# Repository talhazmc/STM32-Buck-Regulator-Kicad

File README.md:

# STM32F4 Test Board with Buck Regulator

This repository contains my KiCad PCB design project for an STM32F4-based test and development board with an integrated buck regulator power section.

The board was designed as a compact embedded systems development platform that includes an STM32F4 microcontroller, programming/debugging interfaces, communication headers, status indicators, and onboard power regulation.

---

## Project Overview

The main purpose of this project was to design a custom STM32F4 test board using KiCad.

The board includes the essential hardware required for working with an STM32F4 microcontroller, such as power input, voltage regulation, SWD programming interface, UART and I2C headers, boot/run control, USB connection, and status LEDs.

This project combines embedded system PCB design and power supply design on a single board.

---

## 3D PCB View

The 3D view shows the physical placement of the STM32F4 microcontroller, SWD header, UART and I2C connectors, USB section, power input terminal, buck regulator components, status LEDs, and mounting holes.

---

## PCB Layout

The PCB layout was created in KiCad.

The STM32F4 microcontroller was placed near the center of the board. Communication and programming headers were positioned around the MCU for easier access. The power regulation section was placed on the right side of the board, close to the power input terminal.

---

## Main Features

- STM32F4 microcontroller-based custom test board
- Integrated buck regulator power section
- SWD programming/debugging connector
- UART communication header
- I2C communication header
- USB connection section
- BOOT and RUN control
- Status LED
- 3.3V power indicator LED
- External power input terminal
- Mounting holes for mechanical fixing

---

## Main Components

- STM32F4 microcontroller
- Buck regulator components
- Inductor
- Power input terminal block
- USB connector section
- SWD header
- UART header
- I2C header
- BOOT switch
- RUN switch
- Status LEDs
- Resistors and capacitors
- Mounting holes

---

## Working Principle

The board is designed around an STM32F4 microcontroller.

The external DC input is connected through the power terminal. The onboard buck regulator section converts the input voltage to the required lower voltage level for the system.

The SWD connector allows the STM32F4 microcontroller to be programmed and debugged. UART and I2C headers provide communication interfaces for external modules, sensors, or other embedded systems.

The BOOT and RUN controls are used during programming, reset, and startup operations. Status LEDs provide visual feedback about the board state and power status.

---

## PCB Design Notes

- The STM32F4 MCU was placed centrally for organized signal routing.
- SWD, UART, and I2C headers were placed near the board edges for easy access.
- The buck regulator section was separated from the microcontroller area.
- Wider traces were used in the power section.
- Mounting holes were added for mechanical stability.
- The board was checked using KiCad 3D Viewer.

---

## What I Learned

Through this project, I gained practical experience in:

- Designing STM32-based embedded system PCBs
- Using KiCad for schematic, PCB layout, and 3D visualization
- Integrating MCU, power, programming, and communication sections
- Designing a buck regulator power stage on the same PCB
- Routing microcontroller signals
- Planning PCB layout for debugging and testing
- Creating a more professional embedded development board structure

---

## Tools and Technologies

- KiCad
- STM32F4
- Buck regulator
- Embedded systems
- PCB design
- SWD programming
- UART communication
- I2C communication
- Power electronics

---

## Author

**Talha Üzümcü**  
Electrical and Electronics Engineer  
GitHub: [talhazmc](https://github.com/talhazmc)

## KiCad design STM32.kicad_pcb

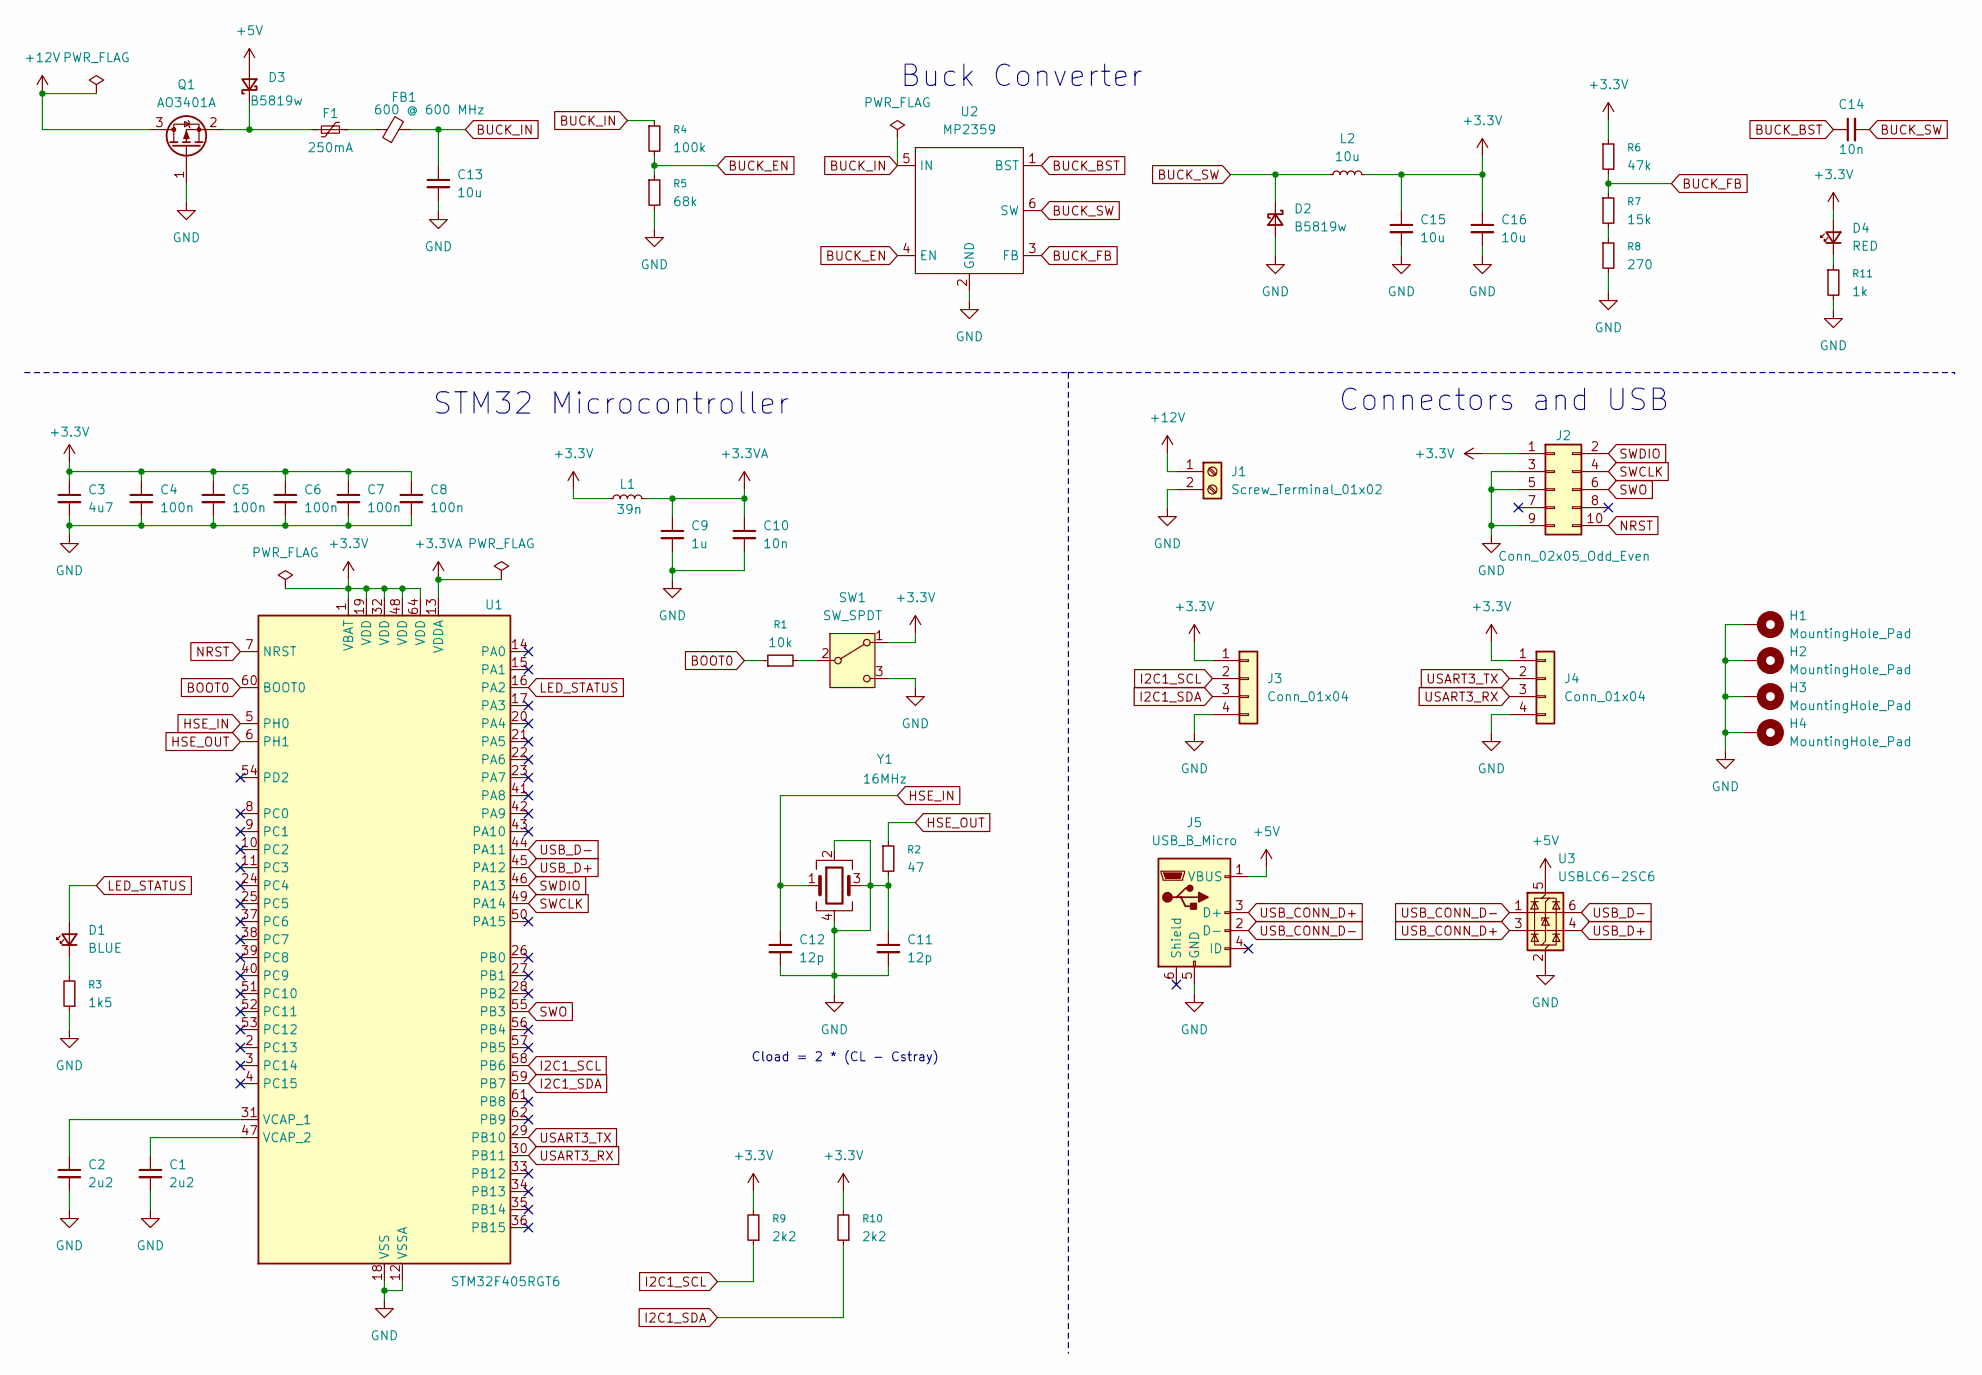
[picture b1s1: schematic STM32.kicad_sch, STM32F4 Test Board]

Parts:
C1, C2: 2u2; C_0603_1608Metric
C3: 4u7; C_0603_1608Metric
C4, C5, C6, C7, C8: 100n; C_0402_1005Metric
C9: 1u; C_0402_1005Metric
C10: 10n; C_0402_1005Metric
C11, C12: 12p; C_0402_1005Metric
C13, C15, C16: 10u; C_1206_3216Metric
C14: 10n; C_0603_1608Metric
D1: BLUE; LED_0603_1608Metric
D2, D3: B5819w; D_SOD-123
D4: RED; LED_0603_1608Metric
F1: 250mA; Fuse_1206_3216Metric
FB1: 600 @ 600 MHz; L_0805_2012Metric
H1, H2, H3, H4: MountingHole_Pad; MountingHole_4.3mm_M4_Pad_Via
J1: Screw_Terminal_01x02; TerminalBlock_Phoenix_PT-1,5-2-3.5-H_1x02_P3.50mm_Horizontal
J2: Conn_02x05_Odd_Even; PinHeader_2x05_P1.27mm_Vertical_SMD
J3, J4: Conn_01x04; Molex_PicoBlade_53048-0410_1x04_P1.25mm_Horizontal
J5: USB_B_Micro; USB_Micro-B_Molex-105017-0001
L1: 39n; L_0402_1005Metric
L2: 10u; L_Sunlord_MWSA0503S
Q1: AO3401A; SOT-23
R1: 10k; R_0402_1005Metric
R2: 47; R_0402_1005Metric
R3: 1k5; R_0603_1608Metric
R4: 100k; R_0603_1608Metric
R5: 68k; R_0603_1608Metric
R6: 47k; R_0603_1608Metric
R7: 15k; R_0603_1608Metric
R8: 270; R_0603_1608Metric
R9, R10: 2k2; R_0402_1005Metric
R11: 1k; R_0603_1608Metric
SW1: SW_SPDT; SW_SPDT_PCM12
U1: STM32F405RGT6; LQFP-64_10x10mm_P0.5mm
U2: MP2359; SOT-23-6
U3: USBLC6-2SC6; SOT-23-6
Y1: 16MHz; Crystal_SMD_3225-4Pin_3.2x2.5mm

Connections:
+3.3V: C3.1, C4.1, C5.1, C6.1, C7.1, C8.1, C15.1, C16.1, D4.2 (A), J2.1, J3.1, J4.1, L1.1, L2.2, R6.1, R9.2, R10.2, SW1.1 (A), U1.1 (VBAT), U1.19 (VDD), U1.32 (VDD), U1.48 (VDD), U1.64 (VDD)
+3.3VA: C9.1, C10.1, L1.2, U1.13 (VDDA)
+5V: D3.2 (A), J5.1 (VBUS), U3.5 (VBUS)
+12V: J1.1, Q1.3 (D)
BOOT0: R1.1, U1.60 (BOOT0)
BUCK_BST: C14.1, U2.1 (BST)
BUCK_EN: R4.2, R5.1, U2.4 (EN)
BUCK_FB: R6.2, R7.1, U2.3 (FB)
BUCK_IN: C13.1, FB1.2, R4.1, U2.5 (IN)
BUCK_SW: C14.2, D2.1 (K), L2.1, U2.6 (SW)
GND: C1.2, C2.2, C3.2, C4.2, C5.2, C6.2, C7.2, C8.2, C9.2, C10.2, C11.1, C11.2, C12.2, C13.2, C15.2, C16.2, D2.2 (A), H1.1, H2.1, H3.1, H4.1, J1.2, J2.3, J2.5, J2.9, J3.4, J4.4, J5.5 (GND), Q1.1 (G), R2.2, R3.1, R5.2, R8.2, R11.2, SW1.3 (C), U1.12 (VSSA), U1.18 (VSS), U1.63 (VSS), U2.2 (GND), U3.2 (GND), Y1.2, Y1.3, Y1.4
HSE_IN: C12.1, U1.5 (PH0), Y1.1
HSE_OUT: R2.1, U1.6 (PH1)
I2C1_SCL: J3.2, R9.1, U1.58 (PB6)
I2C1_SDA: J3.3, R10.1, U1.59 (PB7)
LED_STATUS: D1.2 (A), U1.16 (PA2)
NRST: J2.10, U1.7 (NRST)
unnamed: D1.1 (K), R3.2
unnamed: D3.1 (K), F1.1, Q1.2 (S)
unnamed: D4.1 (K), R11.1
unnamed: F1.2, FB1.1
unnamed: R7.2, R8.1
unnamed: R1.2, SW1.2 (B)
unnamed: C2.1, U1.31 (VCAP_1)
unnamed: C1.1, U1.47 (VCAP_2)
SWCLK: J2.4, U1.49 (PA14)
SWDIO: J2.2, U1.46 (PA13)
SWO: J2.6, U1.55 (PB3)
USART3_RX: J4.3, U1.30 (PB11)
USART3_TX: J4.2, U1.29 (PB10)
USB_CONN_D+: J5.3 (D+), U3.3 (I/O2)
USB_CONN_D-: J5.2 (D-)
USB_CONN_D-: U3.1 (I/O1)
USB_D+: U1.45 (PA12), U3.4 (I/O2)
USB_D-: U1.44 (PA11), U3.6 (I/O1)

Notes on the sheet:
Buck Converter
STM32 Microcontroller
Connectors and USB
Cload = 2 * (CL - Cstray)

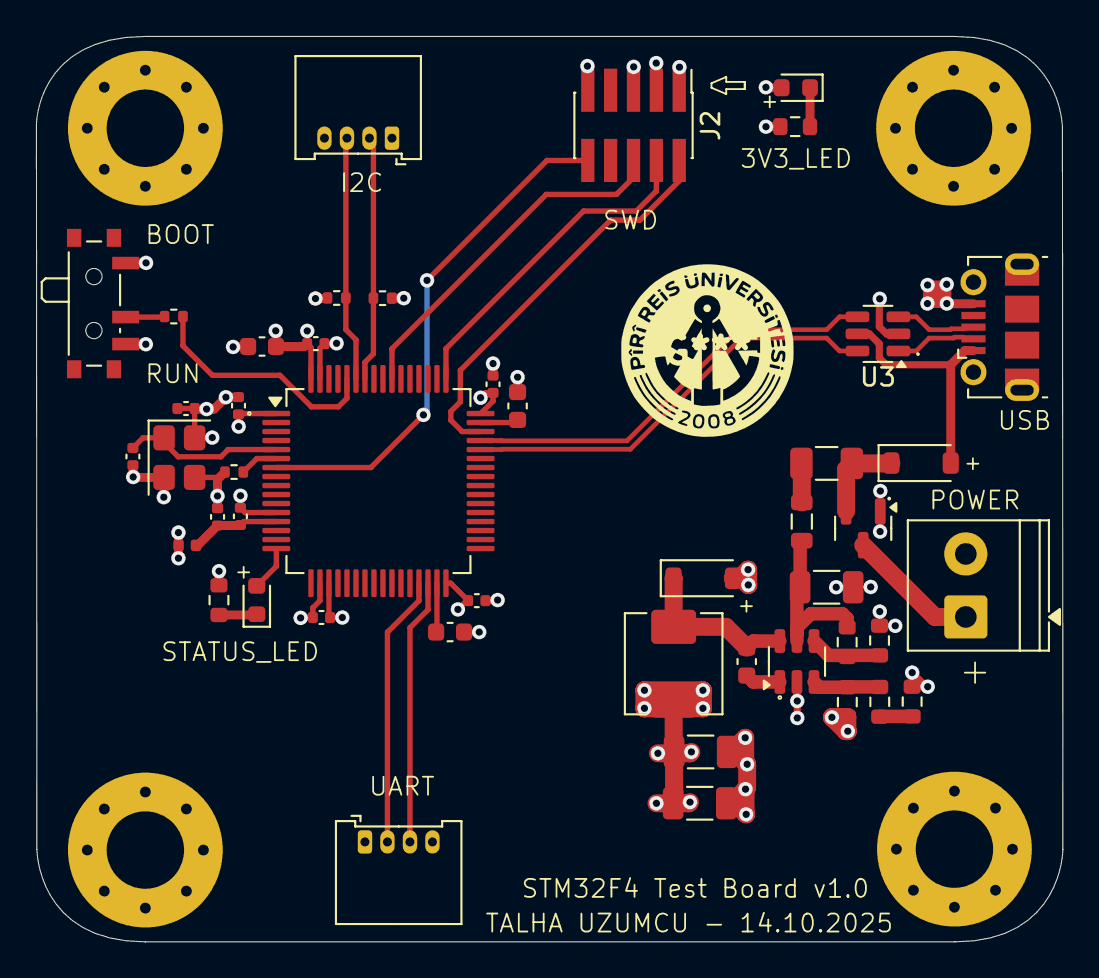
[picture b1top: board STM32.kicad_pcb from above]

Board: 4 copper layers, 57.0 x 50.3 mm, 50 parts (0 on the bottom side), 33 nets.

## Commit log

2026-06-24 images
